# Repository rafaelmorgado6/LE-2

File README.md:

# LE-2

Laboratórios de Eletrónica II

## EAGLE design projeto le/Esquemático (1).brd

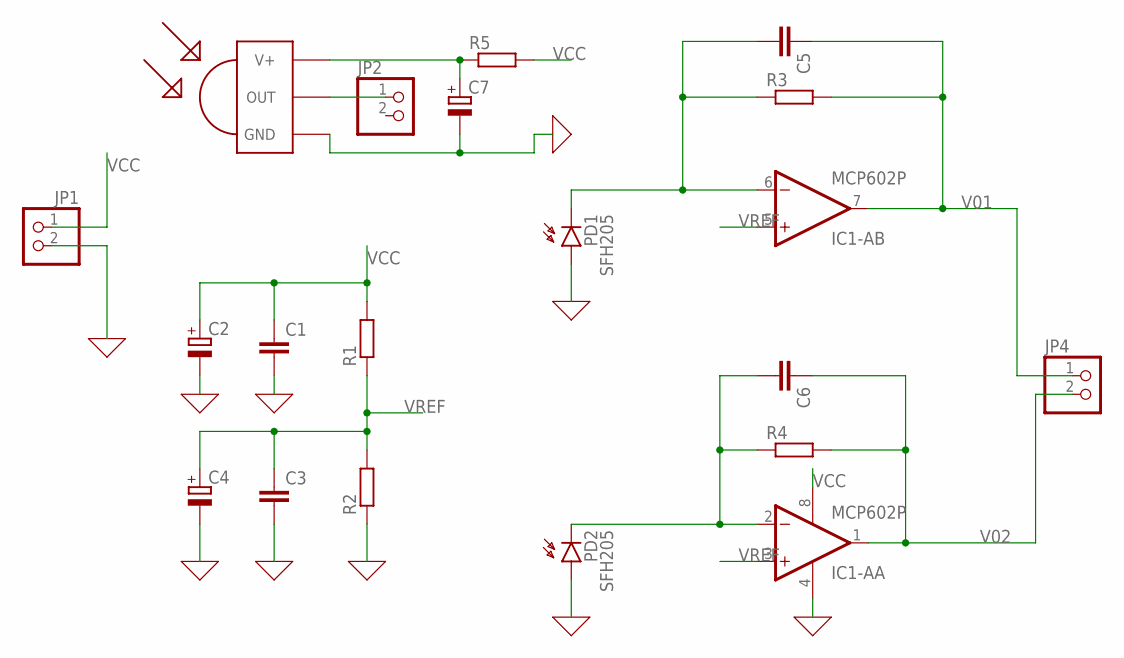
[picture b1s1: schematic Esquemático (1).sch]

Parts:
C1, C3, C5, C6: C-EU025-025X050; C025-025X050
C2, C4, C7: CPOL-EUE2.5-6; E2,5-6
IC1-A: MCP602P; DIL08
JP1, JP2, JP4: PINHD-1X2; 1X02
PD1, PD2: SFH205
R1, R2, R3, R4, R5: R-EU_0207/10; 0207/10
U$1: TSOP4856; TSOP18XX

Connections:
0: C1.2, C2.-, C3.2, C4.-, C7.-, IC1-A.4 (V-), JP1.2, PD1.A, PD2.A, R2.1, U$1.GND
unnamed: C7.+, R5.1, U$1.VCC (V+)
unnamed: JP2.1, U$1.OUT
unnamed: C6.2, IC1-A.2 (-IN), PD2.K (C), R4.1
unnamed: C5.2, IC1-A.6 (-IN), PD1.K (C), R3.1
V01: C5.1, IC1-A.7 (OUT), JP4.1, R3.2
V02: C6.1, IC1-A.1 (OUT), JP4.2, R4.2
VCC: C1.1, C2.+, IC1-A.8 (V+), JP1.1, R1.2, R5.2
VREF: C3.1, C4.+, IC1-A.3 (+IN), IC1-A.5 (+IN), R1.1, R2.2

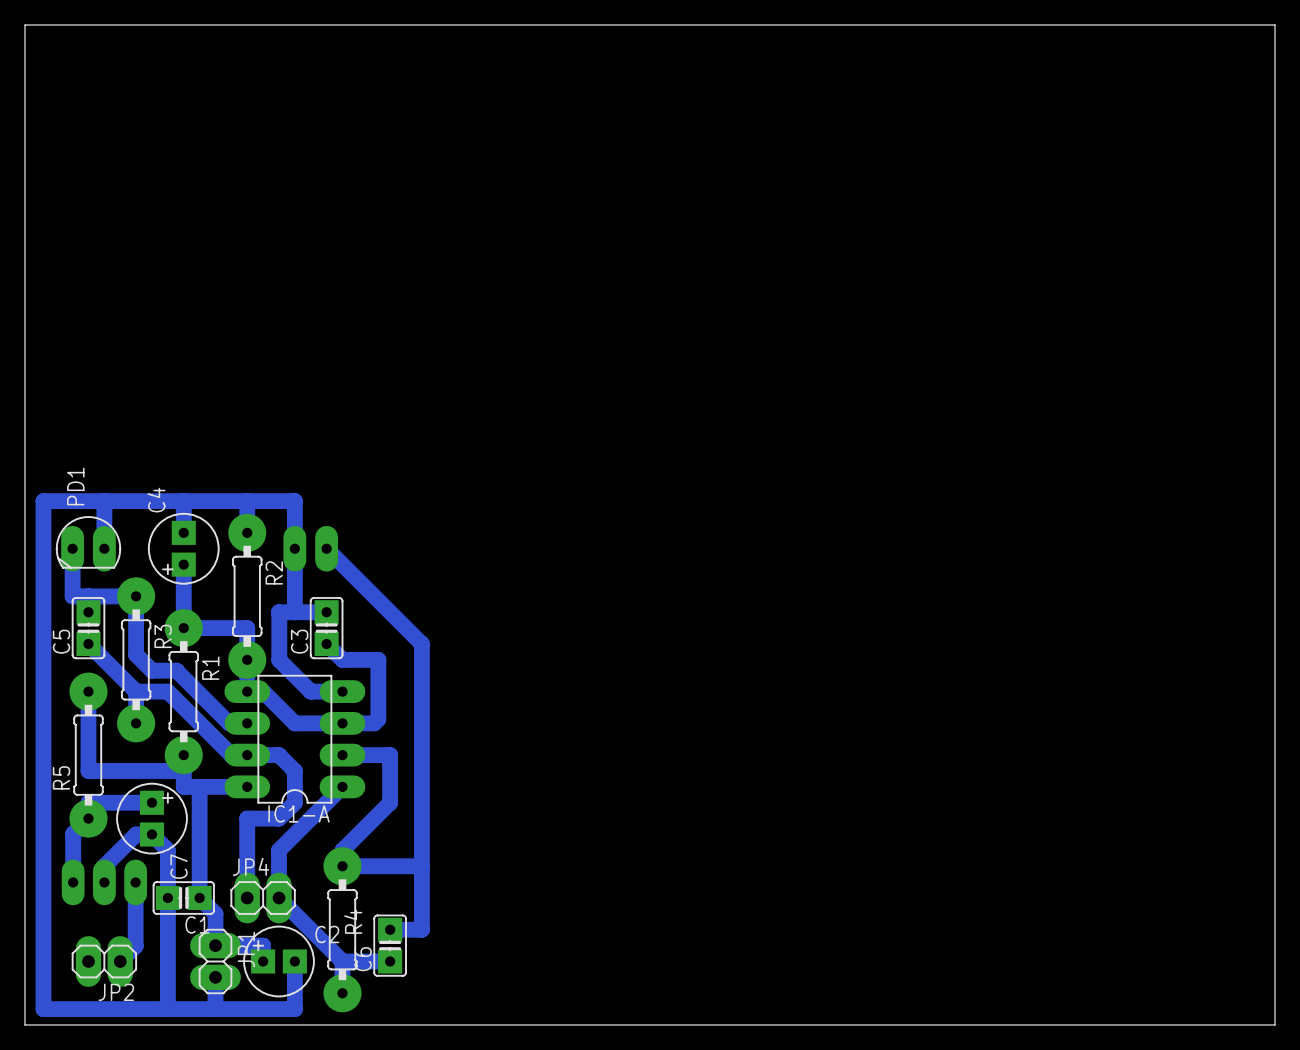
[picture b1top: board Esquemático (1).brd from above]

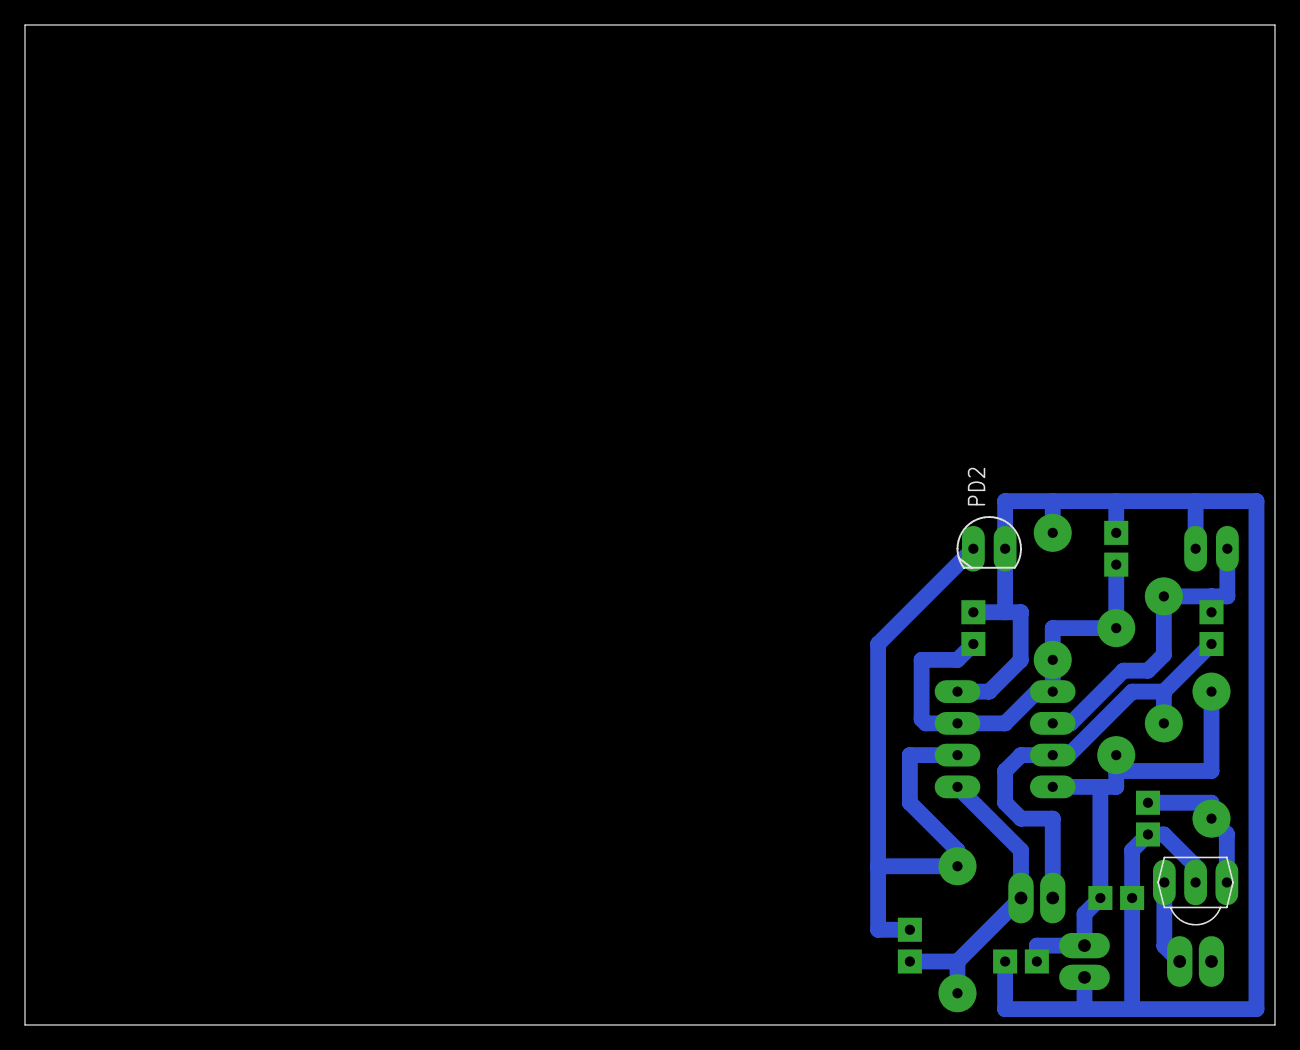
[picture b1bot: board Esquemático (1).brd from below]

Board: 2 copper layers, 100.0 x 80.0 mm, 19 parts (2 on the bottom side), 9 nets.
